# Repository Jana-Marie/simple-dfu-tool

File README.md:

# simple-dfu-tool

Just a smol board to temporarily break a projects power supply to let it boot into DFU mode without unplugging the whole USB cable.

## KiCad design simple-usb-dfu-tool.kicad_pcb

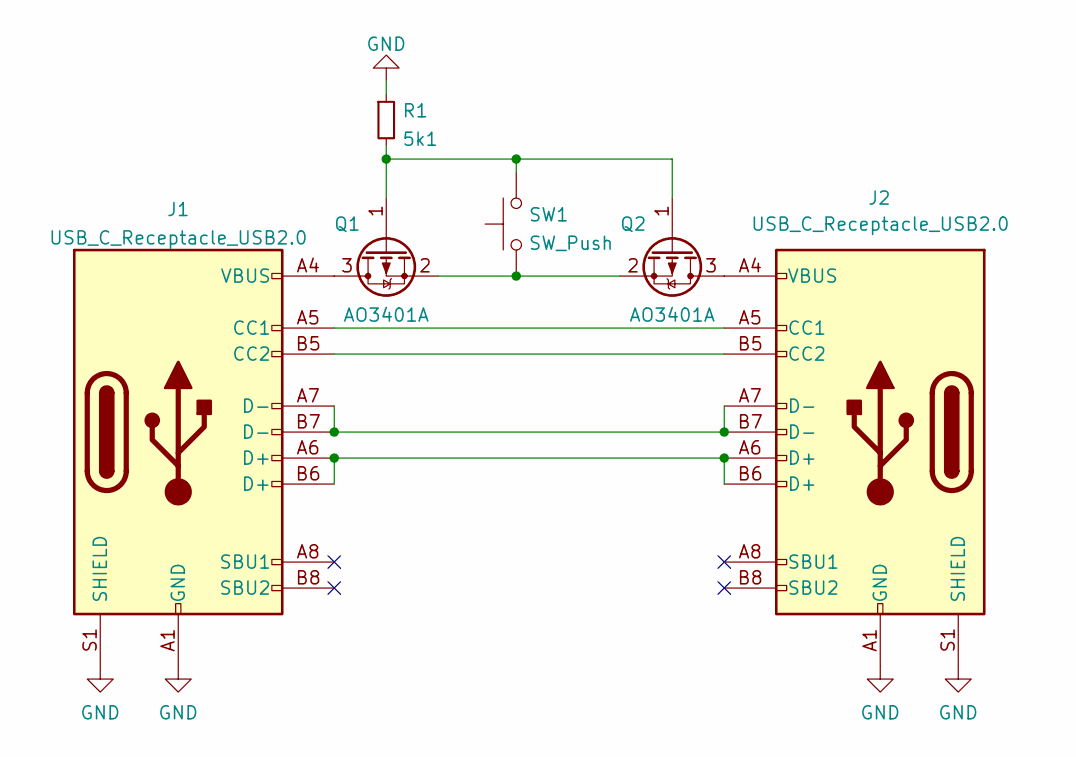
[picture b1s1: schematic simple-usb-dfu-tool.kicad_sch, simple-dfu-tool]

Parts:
J1, J2: USB_C_Receptacle_USB2.0; USB-C 16Pin
Q1, Q2: AO3401A; SOT-23
R1: 5k1; R_0402
SW1: SW_Push; PTS810_LL

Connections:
GND: J1.A1 (GND), J1.A12 (GND), J1.B1 (GND), J1.B12 (GND), J1.S1 (SHIELD), J2.A1 (GND), J2.A12 (GND), J2.B1 (GND), J2.B12 (GND), J2.S1 (SHIELD), R1.1
unnamed: J1.A4 (VBUS), J1.A9 (VBUS), J1.B4 (VBUS), J1.B9 (VBUS), Q1.3 (D)
unnamed: J1.A5 (CC1), J2.A5 (CC1)
unnamed: J1.A6 (D+), J1.B6 (D+), J2.A6 (D+), J2.B6 (D+)
unnamed: J1.A7 (D-), J1.B7 (D-), J2.A7 (D-), J2.B7 (D-)
unnamed: J1.B5 (CC2), J2.B5 (CC2)
unnamed: J2.A4 (VBUS), J2.A9 (VBUS), J2.B4 (VBUS), J2.B9 (VBUS), Q2.3 (D)
unnamed: Q1.2 (S), Q2.2 (S), SW1.1
unnamed: Q1.1 (G), Q2.1 (G), R1.2, SW1.2

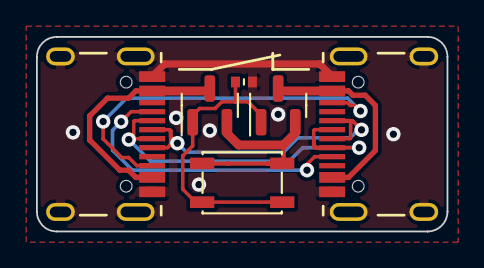
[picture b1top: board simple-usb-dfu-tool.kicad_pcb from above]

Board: 2 copper layers, 22.8 x 10.8 mm, 6 parts (0 on the bottom side), 9 nets.

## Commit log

2022-11-27 added gitignore
2022-11-27 added images
2022-11-27 added kicad files
2022-11-27 added license
